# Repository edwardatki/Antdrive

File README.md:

# Antdrive
A lightweight motor driver designed for antweight combat robots. Setup instructions are available [here](https://github.com/edwardatki/Antdrive/blob/master/documentation/guide.pdf).

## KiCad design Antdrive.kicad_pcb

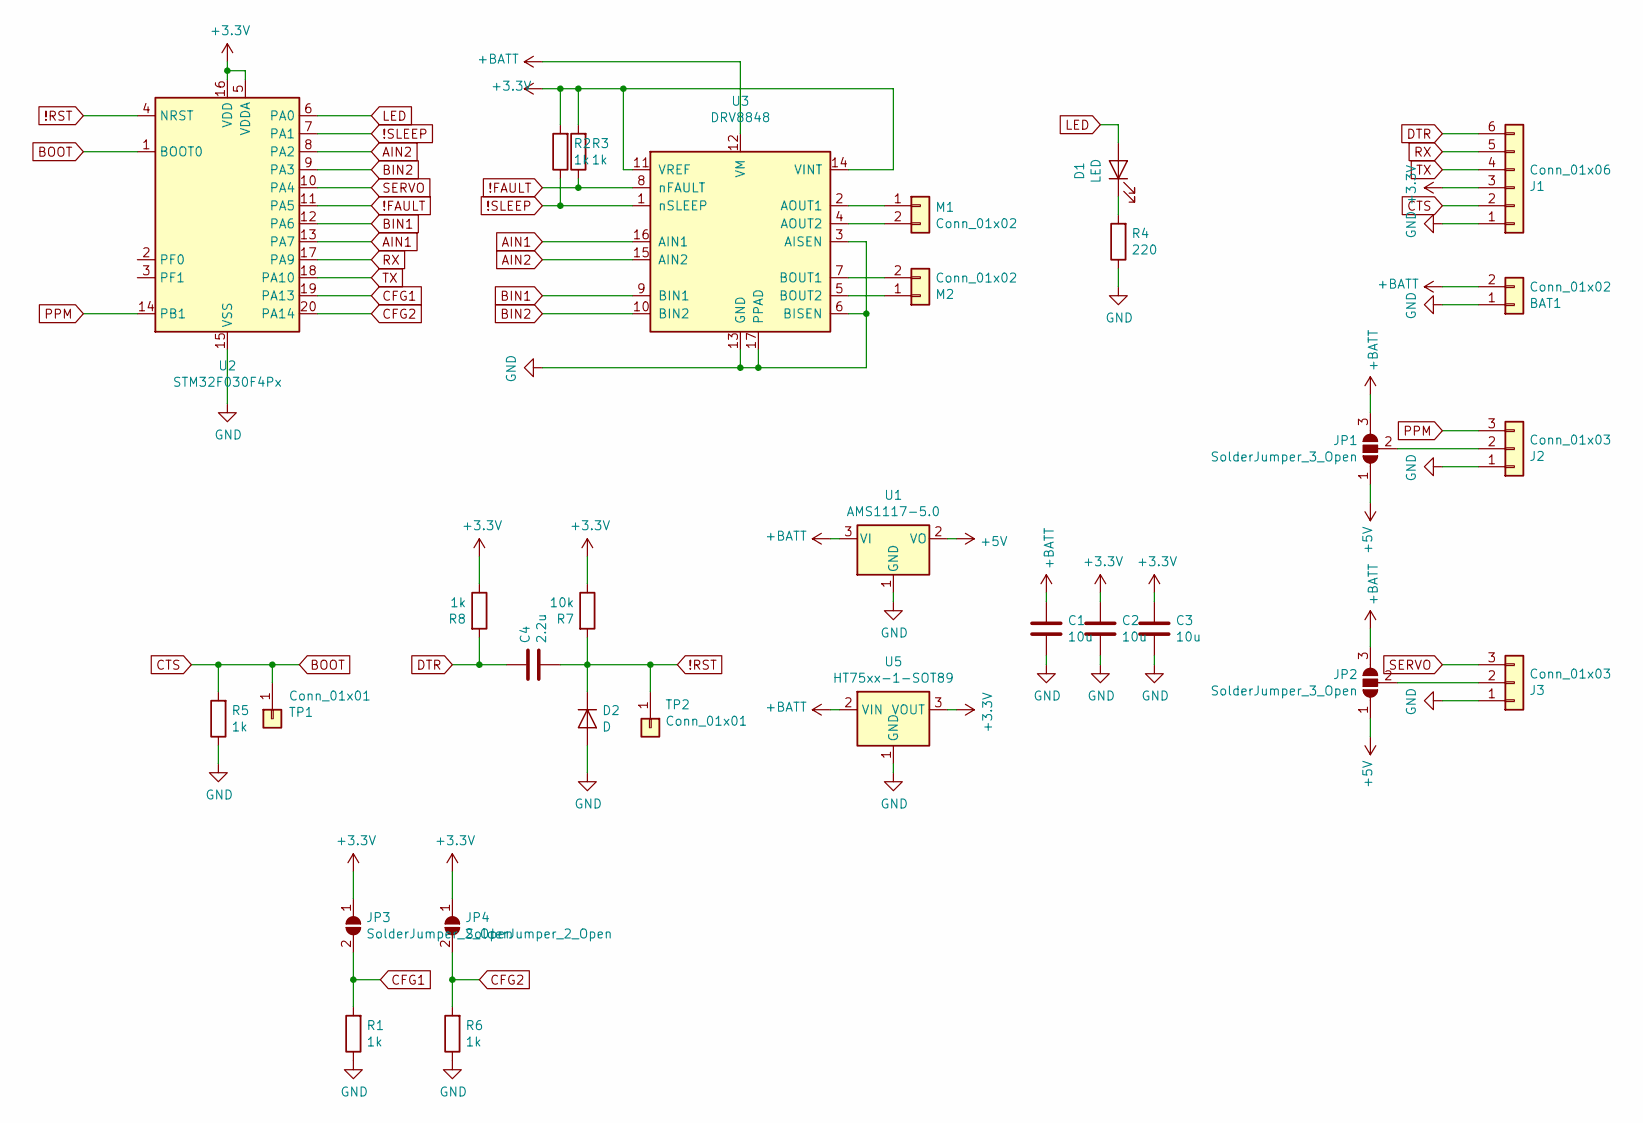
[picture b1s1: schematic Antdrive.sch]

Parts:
BAT1: Conn_01x02; PinHeader_1x02_P2.54mm_Vertical
C1, C2, C3: 10u; C_0603_1608Metric
C4: 2.2u; C_0603_1608Metric
D1: LED; LED_0603_1608Metric
D2: D; D_SOD-323
J1: Conn_01x06; PinSocket_1x06_P2.54mm_Vertical
J2, J3: Conn_01x03; PinHeader_1x03_P2.54mm_Vertical
JP1, JP2: SolderJumper_3_Open; SolderJumper-3_P1.3mm_Open_Pad1.0x1.5mm_NumberLabels
JP3, JP4: SolderJumper_2_Open; SolderJumper-2_P1.3mm_Open_Pad1.0x1.5mm
M1, M2: Conn_01x02; PinHeader_1x02_P2.54mm_Vertical
R1, R2, R3, R5, R6, R8: 1k; R_0603_1608Metric
R4: 220; R_0603_1608Metric
R7: 10k; R_0603_1608Metric
TP1, TP2: Conn_01x01; TestPoint_Pad_D2.0mm
U1: AMS1117-5.0; SOT-223-3_TabPin2
U2: STM32F030F4Px; TSSOP-20_4.4x6.5mm_P0.65mm
U3: DRV8848; TSSOP-16-1EP_4.4x5mm_P0.65mm
U5: HT75xx-1-SOT89; SOT-89-3

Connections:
!FAULT: R3.1, U2.11 (PA5), U3.8 (nFAULT)
!RST: C4.2, D2.1 (K), R7.2, TP2.1, U2.4 (NRST)
!SLEEP: R2.1, U2.7 (PA1), U3.1 (nSLEEP)
+3V3: C2.1, C3.1, J1.3, JP3.1 (A), JP4.1 (A), R2.2, R3.2, R7.1, R8.1, U2.5 (VDDA), U2.16 (VDD), U3.11 (VREF), U3.14 (VINT), U5.3 (VOUT)
+5V: JP1.1 (A), JP2.1 (A), U1.2 (VO)
+BATT: BAT1.2, C1.1, JP1.3 (B), JP2.3 (B), U1.3 (VI), U3.12 (VM), U5.2 (VIN)
AIN1: U2.13 (PA7), U3.16 (AIN1)
AIN2: U2.8 (PA2), U3.15 (AIN2)
BIN1: U2.12 (PA6), U3.9 (BIN1)
BIN2: U2.9 (PA3), U3.10 (BIN2)
BOOT: J1.2, R5.2, TP1.1, U2.1 (BOOT0)
CFG1: JP3.2 (B), R1.2, U2.19 (PA13)
CFG2: JP4.2 (B), R6.2, U2.20 (PA14)
DTR: C4.1, J1.6, R8.2
GND: BAT1.1, C1.2, C2.2, C3.2, D2.2 (A), J1.1, J2.1, J3.1, R1.1, R4.1, R5.1, R6.1, U1.1 (GND), U2.15 (VSS), U3.3 (AISEN), U3.6 (BISEN), U3.13 (GND), U3.17 (PPAD), U5.1 (GND)
LED: D1.2 (A), U2.6 (PA0)
unnamed: D1.1 (K), R4.2
unnamed: J2.2, JP1.2 (C)
unnamed: J3.2, JP2.2 (C)
unnamed: M1.1, U3.2 (AOUT1)
unnamed: M1.2, U3.4 (AOUT2)
unnamed: M2.1, U3.5 (BOUT2)
unnamed: M2.2, U3.7 (BOUT1)
PPM: J2.3, U2.14 (PB1)
RX: J1.5, U2.17 (PA9)
SERVO: J3.3, U2.10 (PA4)
TX: J1.4, U2.18 (PA10)

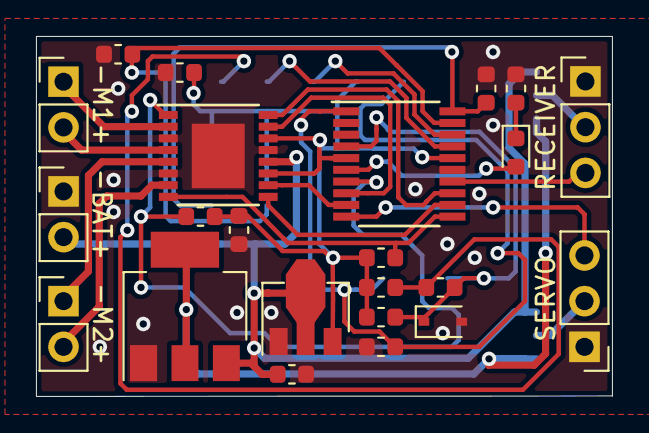
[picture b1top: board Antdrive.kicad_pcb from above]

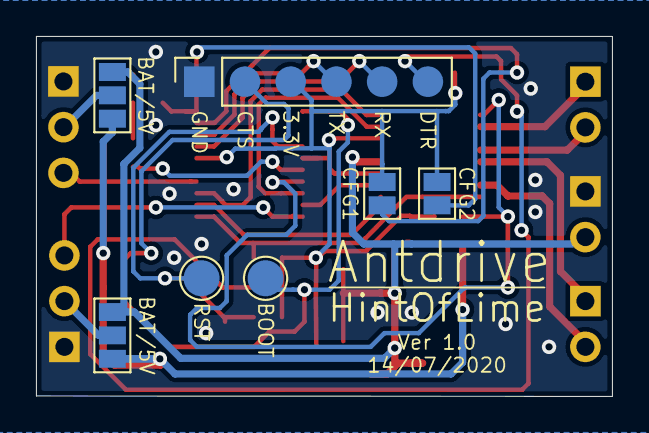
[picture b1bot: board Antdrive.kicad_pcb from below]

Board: 2 copper layers, 32.0 x 20.0 mm, 30 parts (7 on the bottom side), 27 nets.

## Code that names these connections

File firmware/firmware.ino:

#include <Servo.h>

// Pin definintions
#define MOT_1A_PIN PA7
#define MOT_1B_PIN PA2
#define MOT_2A_PIN PA6
#define MOT_2B_PIN PA3
#define MOT_SLEEP_PIN PA1
#define MOT_FAULT_PIN PA5
#define LED_PIN PA0
#define SERVO_PIN PA4
#define PPM_PIN PB1
#define CFG1_PIN PA13
#define CFG2_PIN PA14

// Deadzone for drive motors
#define DEADZONE 10

// Config options
static bool INPUT_MODE;
static bool MIXING;

// Servo object for outputting throttle channel
Servo weapon;

// PPM decoding configuration
#define PPM_MIN_SYNC 5000
#define PPM_MIN_PULSE 600
#define PPM_MAX_PULSE 1600

// PWM decoding configuration
#define PWM_MIN_PULSE 1000
#define PWM_MAX_PULSE 2000

#define CHANNELS 8
static int channels[CHANNELS];

static int lastUpdate;
static bool haveUpdate;

void ppmInterrupt () {
  static char counter = 0;
  static unsigned long startMicros = 0;

  bool val = digitalRead(PPM_PIN);
  
  if (val) {
    startMicros = micros();
  } else {
    int duration = micros() - startMicros;
    if (duration > PPM_MIN_SYNC) {
      counter = 0;
    } else {
      duration =  constrain(duration, PPM_MIN_PULSE, PPM_MAX_PULSE);
      channels[counter] = map(duration, PPM_MIN_PULSE, PPM_MAX_PULSE, -255, 255);
      counter += 1;
    }

    lastUpdate = millis();
    haveUpdate = true;
  }
}

void pwmInterruptA () {
  static unsigned long startMicros = 0;

  bool val = digitalRead(PPM_PIN);
  
  if (val) {
    startMicros = micros();
  } else {
    int duration = constrain(micros() - startMicros, PWM_MIN_PULSE, PPM_MAX_PULSE);
    channels[0] = map(duration, PWM_MIN_PULSE, PWM_MAX_PULSE, -255, 255);

    lastUpdate = millis();
    haveUpdate = true;
  }
}

void pwmInterruptB () {
  static unsigned long startMicros = 0;
  
  bool val = digitalRead(SERVO_PIN);
  
  if (val) {
    startMicros = micros();
  } else {
    int duration = constrain(micros() - startMicros, PWM_MIN_PULSE, PPM_MAX_PULSE);
    channels[1] = map(duration, PWM_MIN_PULSE, PWM_MAX_PULSE, -255, 255);

    lastUpdate = millis();
    haveUpdate = true;
  }
}

// Set motor 0 or 1 to a speed between -255 and 255
void setMotor (bool motor, int value) {
  if (motor == 0) {
    if (value > 0+DEADZONE) {
      analogWrite(MOT_1A_PIN, abs(value));
      digitalWrite(MOT_1B_PIN, LOW);
    } else if (value < 0-DEADZONE) {
      analogWrite(MOT_1A_PIN, 255-abs(value));
      digitalWrite(MOT_1B_PIN, HIGH);
    } else {
      analogWrite(MOT_1A_PIN, 255);
      digitalWrite(MOT_1B_PIN, HIGH);
    }
  } else {
    if (value > 0+DEADZONE) {
      analogWrite(MOT_2A_PIN, abs(value));
      digitalWrite(MOT_2B_PIN, LOW);
    } else if (value < 0-DEADZONE) {
      analogWrite(MOT_2A_PIN, 255-abs(value));
      digitalWrite(MOT_2B_PIN, HIGH);
    } else {
      analogWrite(MOT_2A_PIN, 255);
      digitalWrite(MOT_2B_PIN, HIGH);
    }
  }
}

void setup() {
  // Set pin modes (don't set PWM pins to OUTPUT on STM32)
  //pinMode(MOT_1A_PIN, OUTPUT);
  pinMode(MOT_1B_PIN, OUTPUT);
  //pinMode(MOT_2A_PIN, OUTPUT);
  pinMode(MOT_2B_PIN, OUTPUT);
  pinMode(MOT_SLEEP_PIN, OUTPUT);
  pinMode(MOT_FAULT_PIN, INPUT);
  pinMode(LED_PIN, OUTPUT);
  //pinMode(SERVO_PIN, OUTPUT);
  pinMode(PPM_PIN, INPUT_PULLUP);
  pinMode(CFG1_PIN, INPUT);
  pinMode(CFG2_PIN, INPUT);

  // Set motors to idle and disable motor driver
  setMotor(0, 0);
  setMotor(1, 0);
  digitalWrite(MOT_SLEEP_PIN, LOW);

  // Set configuration varialbles from config jumpers
  INPUT_MODE = digitalRead(CFG1_PIN);
  MIXING = digitalRead(CFG2_PIN);

  // Flash LED to indicate ready
  digitalWrite(LED_PIN, HIGH);
  delay(50);
  digitalWrite(LED_PIN, LOW);
  delay(100);
  digitalWrite(LED_PIN, HIGH);
  delay(50);
  digitalWrite(LED_PIN, LOW);
  delay(100);

  if (INPUT_MODE) {
    pinMode(SERVO_PIN, INPUT_PULLUP);
    attachInterrupt(PPM_PIN, pwmInterruptA, CHANGE);
    attachInterrupt(SERVO_PIN, pwmInterruptB, CHANGE);
  } else {
    attachInterrupt(PPM_PIN, ppmInterrupt, CHANGE);
  }
}

void loop() {
  // Fault check disabled because it's always comes back positive
  // Driver still operates so the problem is between driver and microcontrollerU
  /*
  // Check for motor driver fault
  if (!digitalRead(MOT_FAULT_PIN)) {
    // If fault detected flash led and exit loop
    digitalWrite(LED_PIN, HIGH);
    delay(50);
    digitalWrite(LED_PIN, LOW);
    delay(50);
    return;
  }
  */

  static bool signalReady = false;
  if (!signalReady) {
    static unsigned int readyCycles = 0;
    if (haveUpdate) readyCycles += 1;
    if (readyCycles > 500) {
      if (!INPUT) {
        // Attach weapon to pin and set to idle
        weapon.attach(SERVO_PIN, 1000, 2000);
        weapon.write(0);
      }

      signalReady = true;
    }
  } else {
    // Check if no signal for a while
    if (abs((int)millis() - lastUpdate) > 200) {
      // No signal so go to failsafe
      
      // Disable LED to indicate receiver disconnected
      digitalWrite(LED_PIN, LOW);
    
      // Disable motor driver
      digitalWrite(MOT_SLEEP_PIN, LOW);
    
      // Set motors to idle
      setMotor(0, 0);
      setMotor(1, 0);
  
      if (!INPUT_MODE) {
        // Set weapon to ilde
        weapon.write(0);
      }
    } else if (haveUpdate) {
      // Still got signal so update motor and weapon outputs
      
      // Enable LED to indicate receiver connected
      digitalWrite(LED_PIN, HIGH);
    
      // Enable motor driver
      digitalWrite(MOT_SLEEP_PIN, HIGH);
    
      // Check if channel mixing is enabled
      if (MIXING) {
        // Mix channels
        int mot1 = min(max(channels[1]-channels[0], -255), 255);
        int mot2 = min(max(channels[1]+channels[0], -255), 255);
        // Set motor speeds
        setMotor(0, mot1);
        setMotor(1, mot2);
      } else {
        // Set motor speeds
        setMotor(0, channels[0]);
        setMotor(1, channels[1]);
      }
  
      if (!INPUT_MODE) {
        // PWM mode
        // Write throttle channel to servo pin for weapon
        weapon.write(map(channels[2], -255, 255, 0, 180));
      }

      haveUpdate = false;
    }
  }
}

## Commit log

2020-05-16 Fix auto reset circuits
2020-05-29 Update schematic
2020-05-29 PCB updated
2020-05-29 Update production files
2020-05-30 Fix production file errors
2020-06-14 Initial firmware
2020-06-15 Ver 0.3
    Added config jumpers and hopefully fixed programming circuitry
2020-07-14 Added documentation
2020-07-14 Update documentation
2020-07-14 Reorganize files
2020-07-14 Add PWM control mode
2020-07-14 Update firmware
2020-07-18 Minor fixes
2020-10-10 Add programming instructions
2020-11-10 Move receiver signal processing into interrupts and enable motor braking
